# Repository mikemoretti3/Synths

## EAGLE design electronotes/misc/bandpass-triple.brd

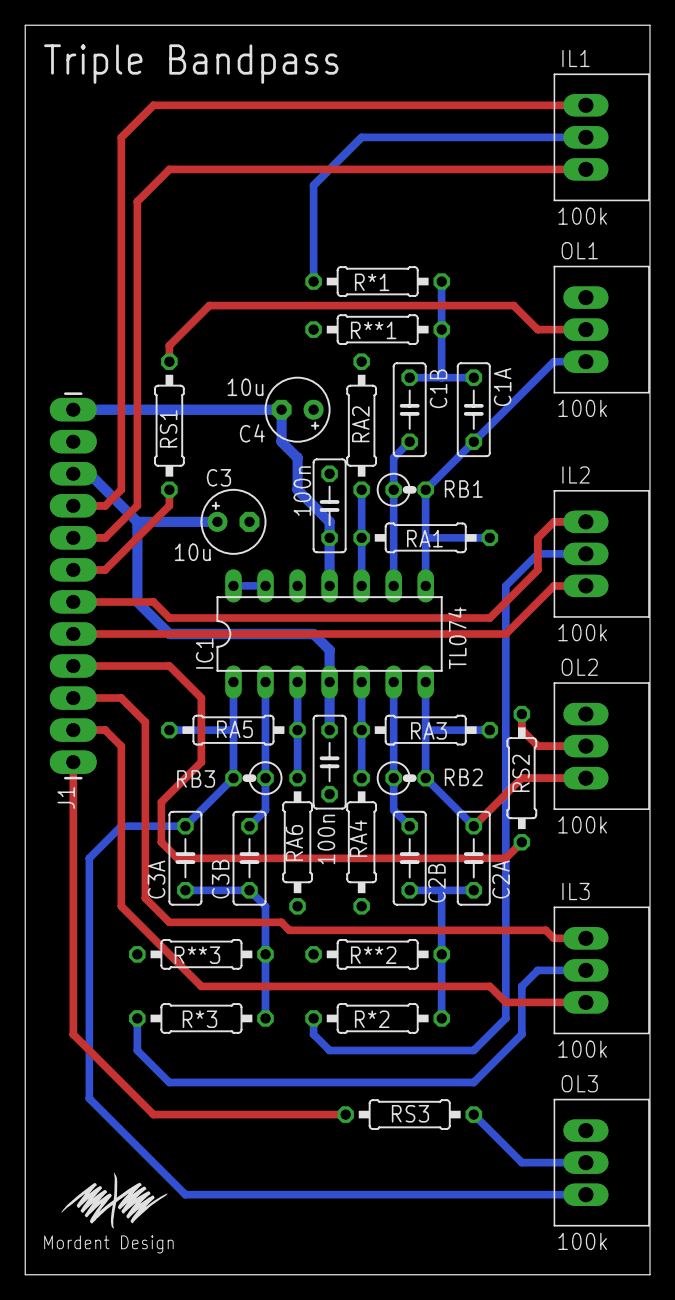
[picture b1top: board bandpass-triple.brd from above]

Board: 2 copper layers, 49.5 x 99.1 mm, 36 parts (0 on the bottom side), 31 nets.

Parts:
C1, C2: 100n; C050-025X075
C1A, C1B, C2A, C2B, C3A, C3B: C050-025X075
C3, C4: 10u; E2,5-5
IC1: TL074; DIL14
IL1, IL2, IL3: 100k; POT-BOURNS-PTD901-2015K
J1: 1X12_LONGPADS
OL1, OL2, OL3: 100k; POT-BOURNS-PTD901-2015K
R*1, R*2, R*3: 0207/10
R**1, R**2, R**3: 0207/10
RA1, RA2, RA3, RA4, RA5, RA6: 0207/10
RB1, RB2, RB3: 0207/2V
RS1, RS2, RS3: 0207/10

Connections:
+12V: C1.1, C3.+, IC1.4, J1.10
-12V: C2.2, C4.-, IC1.11, J1.12
GND: C1.2, C2.1, C3.-, C4.+, IC1.12, J1.11, OL1.3, OL2.3, OL3.3, R**1.1, R**2.1, R**3.1, RA2.1, RA4.1, RA6.1
IN1: IL1.1, J1.8
IN2: IL2.1, J1.5
IN3: IL3.1, J1.2
unnamed: C1B.2, IC1.9, RB1.1
unnamed: C1A.2, IC1.8, OL1.1, RA1.2, RB1.2
unnamed: C1A.1, C1B.1, R*1.2, R**1.2
unnamed: IC1.10, RA1.1, RA2.2
unnamed: C2B.2, IC1.6, RB2.1
unnamed: C2A.2, IC1.7, OL2.1, RA3.2, RB2.2
unnamed: C2A.1, C2B.1, R*2.2, R**2.2
unnamed: IC1.5, RA3.1, RA4.2
unnamed: C3B.2, IC1.2, RB3.1
unnamed: C3A.2, IC1.1, OL3.1, RA5.2, RB3.2
unnamed: C3A.1, C3B.1, R*3.2, R**3.2
unnamed: IC1.3, RA5.1, RA6.2
unnamed: IC1.13, IC1.14
unnamed: IL1.2, R*1.1
unnamed: IL2.2, R*2.1
unnamed: IL3.2, R*3.1
unnamed: OL1.2, RS1.1
unnamed: OL2.2, RS2.1
unnamed: OL3.2, RS3.1
OUT1: J1.7, RS1.2
OUT2: J1.4, RS2.2
OUT3: J1.1, RS3.2
QIN1: IL1.3, J1.9
QIN2: IL2.3, J1.6
QIN3: IL3.3, J1.3

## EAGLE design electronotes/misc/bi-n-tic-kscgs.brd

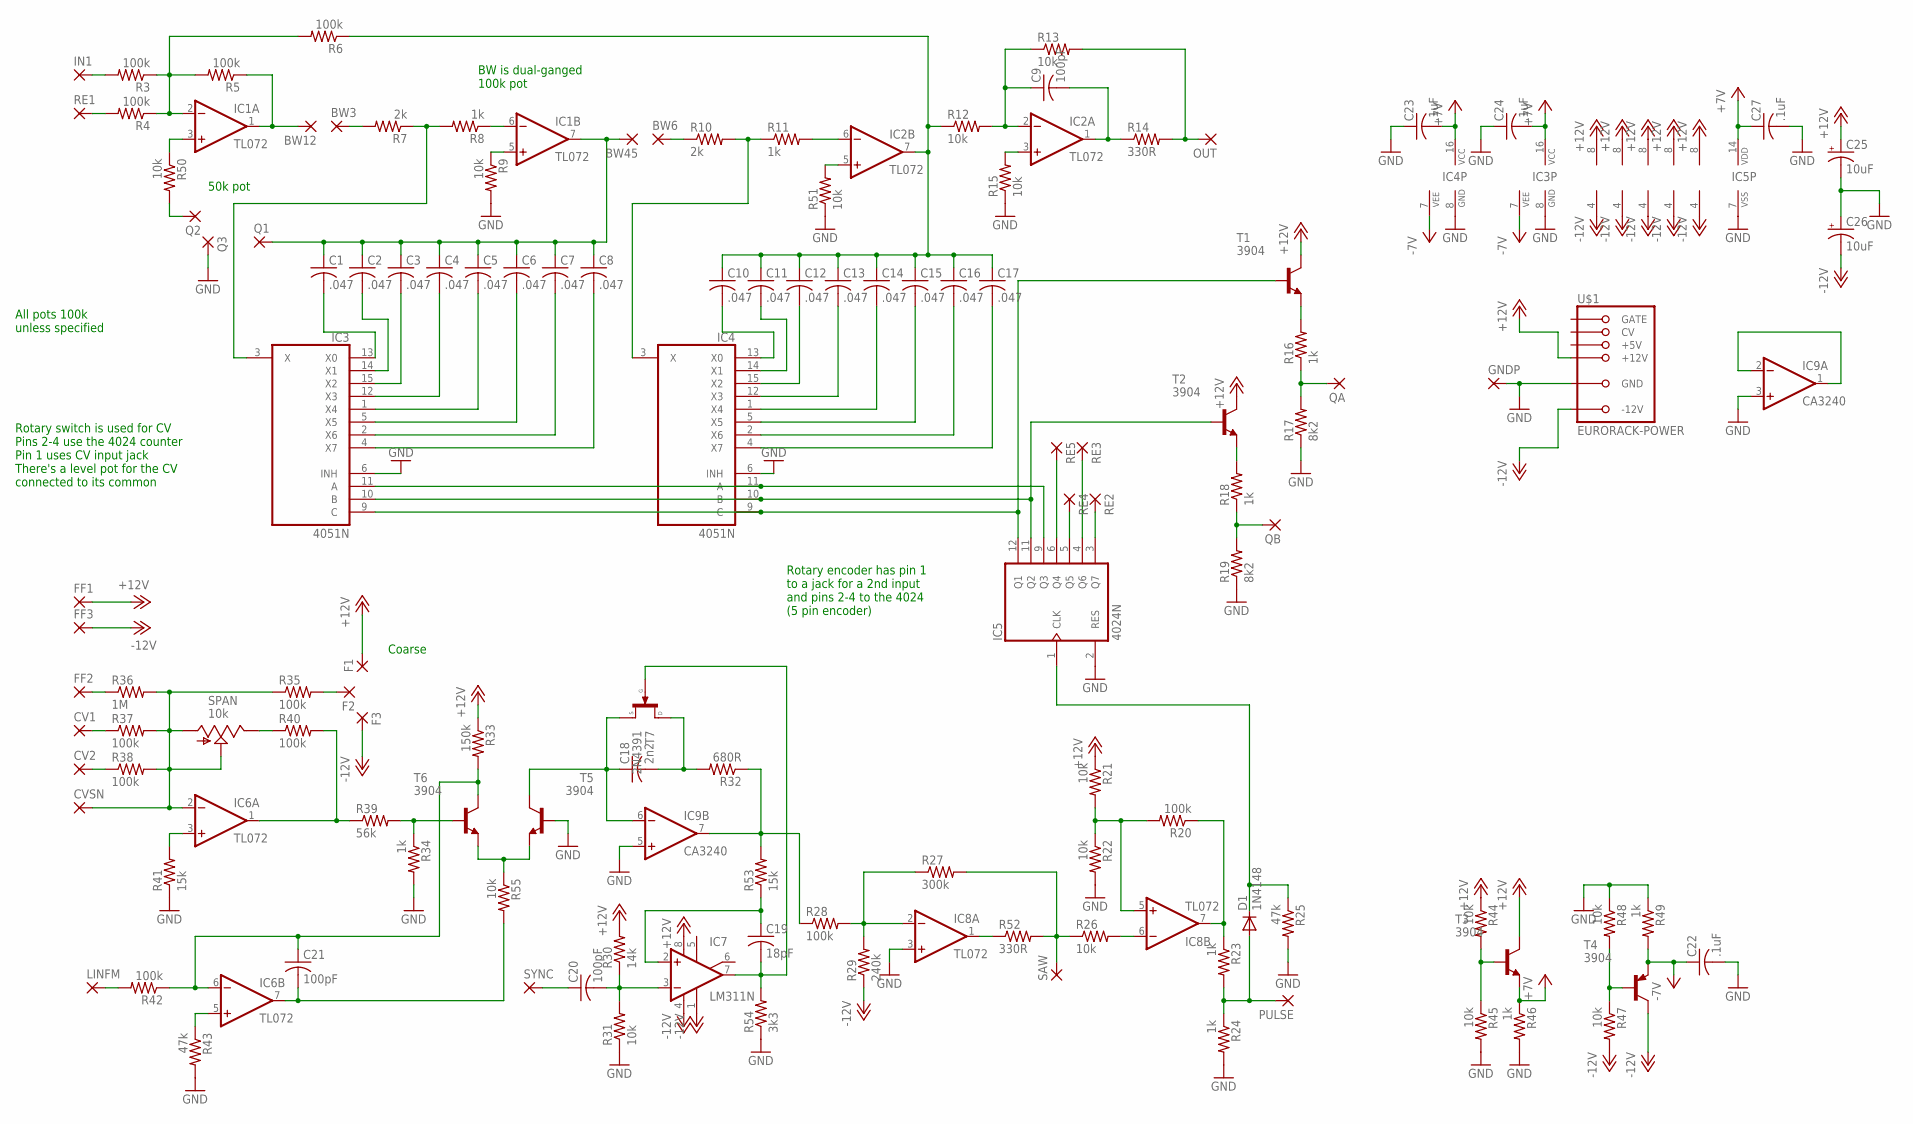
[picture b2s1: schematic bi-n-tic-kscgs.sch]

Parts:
BW3, BW6, BW12, BW45: 2,54/1,0
C1, C2, C3, C4, C5, C6, C7, C8, C10, C11, C12, C13, C14, C15, C16, C17: .047; C050-025X075
C9, C20, C21: 100pF; C050-025X075
C18: 2n2; C050-025X075
C19: 18pF; C050-025X075
C22, C23, C24, C27: .1uF; C050-025X075
C25, C26: 10uF; E2,5-5
CV1, CV2: 2,54/1,0
CVSN: 2,54/1,0
D1: 1N4148; DO35-7
F1, F2, F3: 2,54/1,0
FF1, FF2, FF3: 2,54/1,0
GNDP: 2,54/1,0
IC1, IC2, IC6, IC8: TL072; DIL08
IC3, IC4: 4051N; DIL16
IC5: 4024N; DIL14
IC7: LM311N; DIL08
IC9: CA3240; DIL08
IN1: 2,54/1,0
LINFM: 2,54/1,0
OUT: 2,54/1,0
PULSE: 2,54/1,0
Q1, Q2, Q3: 2,54/1,0
QA: 2,54/1,0
QB: 2,54/1,0
R3, R4, R5, R6, R20, R28, R35, R37, R38, R40, R42: 100k; 0207/10
R7, R10: 2k; 0207/10
R8, R11, R16, R18, R23, R24, R34, R46, R49: 1k; 0207/10
R9, R12, R13, R15, R21, R22, R26, R31, R44, R45, R47, R48, R50, R51, R55: 10k; 0207/10
R14, R52: 330R; 0207/10
R17, R19: 8k2; 0207/10
R25, R43: 47k; 0207/10
R27: 300k; 0207/10
R29: 240k; 0207/10
R30: 14k; 0207/10
R32: 680R; 0207/10
R33: 150k; 0207/10
R36: 1M; 0207/10
R39: 56k; 0207/10
R41, R53: 15k; 0207/10
R54: 3k3; 0207/10
RE1, RE2, RE3, RE4, RE5: 2,54/1,0
SAW: 2,54/1,0
SPAN: 10k; RJ9W
SYNC: 2,54/1,0
T1, T2, T3, T4, T5, T6: 3904; TO92-EBC
T7: 2N4391; TO18E
U$1: EURORACK-POWER; PINSHRD_PTH_2X8

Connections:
+7V: C23.2, C24.2, C27.1, IC3.16 (VCC), IC4.16 (VCC), IC5.14 (VDD), R46.1, T3.E
+12V: C25.+, F1.1, FF1.1, IC1.8 (V+), IC2.8 (V+), IC6.8 (V+), IC7.8 (V+), IC8.8 (V+), IC9.8 (V+), R21.1, R30.2, R33.1, R44.1, T1.C, T2.C, T3.C, U$1.+12V@1 (+12V), U$1.+12V@2 (+12V)
-7V: C22.1, IC3.7 (VEE), IC4.7 (VEE), R49.2, T4.E
-12V: C26.-, F3.1, FF3.1, IC1.4 (V-), IC2.4 (V-), IC6.4 (V-), IC7.1 (GND), IC7.4 (V-), IC8.4 (V-), IC9.4 (V-), R29.1, R47.2, T4.C, U$1.-12V@1 (-12V), U$1.-12V@2 (-12V)
GND: C22.2, C23.1, C24.1, C25.-, C26.+, C27.2, GNDP.1, IC3.6 (INH), IC3.8 (GND), IC4.6 (INH), IC4.8 (GND), IC5.2 (RES), IC5.7 (VSS), IC8.3 (+IN), IC9.3 (+IN), IC9.5 (+IN), Q3.1, R9.2, R15.1, R17.1, R19.1, R22.2, R24.2, R25.2, R31.1, R34.2, R41.1, R43.2, R45.2, R46.2, R48.1, R49.1, R51.1, R54.1, T5.B, U$1.GND@1 (GND), U$1.GND@2 (GND), U$1.GND@3 (GND), U$1.GND@4 (GND), U$1.GND@5 (GND), U$1.GND@6 (GND)
unnamed: IC8.2 (-IN), R27.1, R28.2, R29.2
unnamed: IC1.2 (-IN), R3.1, R4.1, R5.2, R6.2
unnamed: BW12.1, IC1.1 (OUT), R5.1
unnamed: IC1.3 (+IN), R50.1
unnamed: Q2.1, R50.2
unnamed: BW3.1, R7.2
unnamed: IC3.3 (X), R7.1, R8.2
unnamed: IC1.6 (-IN), R8.1
unnamed: C1.2, IC3.13 (X0)
unnamed: C2.2, IC3.14 (X1)
unnamed: C3.2, IC3.15 (X2)
unnamed: C4.2, IC3.12 (X3)
unnamed: C5.2, IC3.1 (X4)
unnamed: C6.2, IC3.5 (X5)
unnamed: C7.2, IC3.2 (X6)
unnamed: C8.2, IC3.4 (X7)
unnamed: BW45.1, C1.1, C2.1, C3.1, C4.1, C5.1, C6.1, C7.1, C8.1, IC1.7 (OUT), Q1.1
unnamed: BW6.1, R10.1
unnamed: IC4.3 (X), R10.2, R11.1
unnamed: IC2.6 (-IN), R11.2
unnamed: C10.1, C11.1, C12.1, C13.1, C14.1, C15.1, C16.1, C17.1, IC2.7 (OUT), R6.1, R12.1
unnamed: C9.1, IC2.2 (-IN), R12.2, R13.1
unnamed: C9.2, IC2.1 (OUT), R14.1
unnamed: OUT.1, R13.2, R14.2
unnamed: IC2.3 (+IN), R15.2
unnamed: IC1.5 (+IN), R9.1
unnamed: C10.2, IC4.13 (X0)
unnamed: C11.2, IC4.14 (X1)
unnamed: C12.2, IC4.15 (X2)
unnamed: C13.2, IC4.12 (X3)
unnamed: C14.2, IC4.1 (X4)
unnamed: C15.2, IC4.5 (X5)
unnamed: C16.2, IC4.2 (X6)
unnamed: C17.2, IC4.4 (X7)
unnamed: IC2.5 (+IN), R51.2
unnamed: R16.2, T1.E
unnamed: FF2.1, R36.1
unnamed: CV1.1, R37.1
unnamed: CV2.1, R38.1
unnamed: LINFM.1, R42.2
unnamed: QA.1, R16.1, R17.2
unnamed: IC3.10 (B), IC4.10 (B), IC5.11 (Q2), T2.B
unnamed: IC3.9 (C), IC4.9 (C), IC5.12 (Q1), T1.B
unnamed: IC3.11 (A), IC4.11 (A), IC5.9 (Q3)
unnamed: R18.2, T2.E
unnamed: QB.1, R18.1, R19.2
unnamed: D1.C, IC5.1 (CLK), R25.1
unnamed: IC9.7 (OUT), R28.1, R32.1, R53.2
unnamed: IC8.5 (+IN), R20.2, R21.2, R22.1
unnamed: IC8.7 (OUT), R20.1, R23.1
unnamed: D1.A, PULSE.1, R23.2, R24.1
unnamed: IC8.6 (-IN), R26.2
unnamed: R26.1, R27.2, R52.2, SAW.1
unnamed: IC8.1 (OUT), R52.1
unnamed: C19.2, IC7.7 (OUT), R54.2, T7.G
unnamed: C18.1, IC9.6 (-IN), T5.C, T7.S
unnamed: C18.2, R32.2, T7.D
unnamed: C19.1, IC7.2 (+IN), R53.1
unnamed: C20.2, IC7.3 (-IN), R30.1, R31.2
unnamed: C20.1, SYNC.1
unnamed: IC9.1 (OUT), IC9.2 (-IN)
unnamed: IC6.5 (+IN), R43.1
unnamed: C21.2, IC6.7 (OUT), R55.2
unnamed: C21.1, IC6.6 (-IN), R33.2, R42.1, T6.C
unnamed: IC6.3 (+IN), R41.2
unnamed: R44.2, R45.1, T3.B
unnamed: CVSN.1, IC6.2 (-IN), R35.1, R36.2, R37.2, R38.2, SPAN.A, SPAN.S
unnamed: R40.1, SPAN.E
unnamed: IC6.1 (OUT), R39.1, R40.2
unnamed: F2.1, R35.2
unnamed: R34.1, R39.2, T6.B
unnamed: IN1.1, R3.2
unnamed: R55.1, T5.E, T6.E
unnamed: R47.1, R48.2, T4.B
unnamed: R4.2, RE1.1
unnamed: IC5.6 (Q4), RE5.1
unnamed: IC5.5 (Q5), RE4.1
unnamed: IC5.3 (Q7), RE2.1
RE3: IC5.4 (Q6), RE3.1

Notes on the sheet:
Rotary encoder has pin 1 to a jack for a 2nd input and pins 2-4 to the 4024 (5 pin encoder)
50k pot
BW is dual-ganged 100k pot
Rotary switch is used for CV Pins 2-4 use the 4024 counter Pin 1 uses CV input jack There's a level pot for the CV connected to its common
Coarse
All pots 100k unless specified

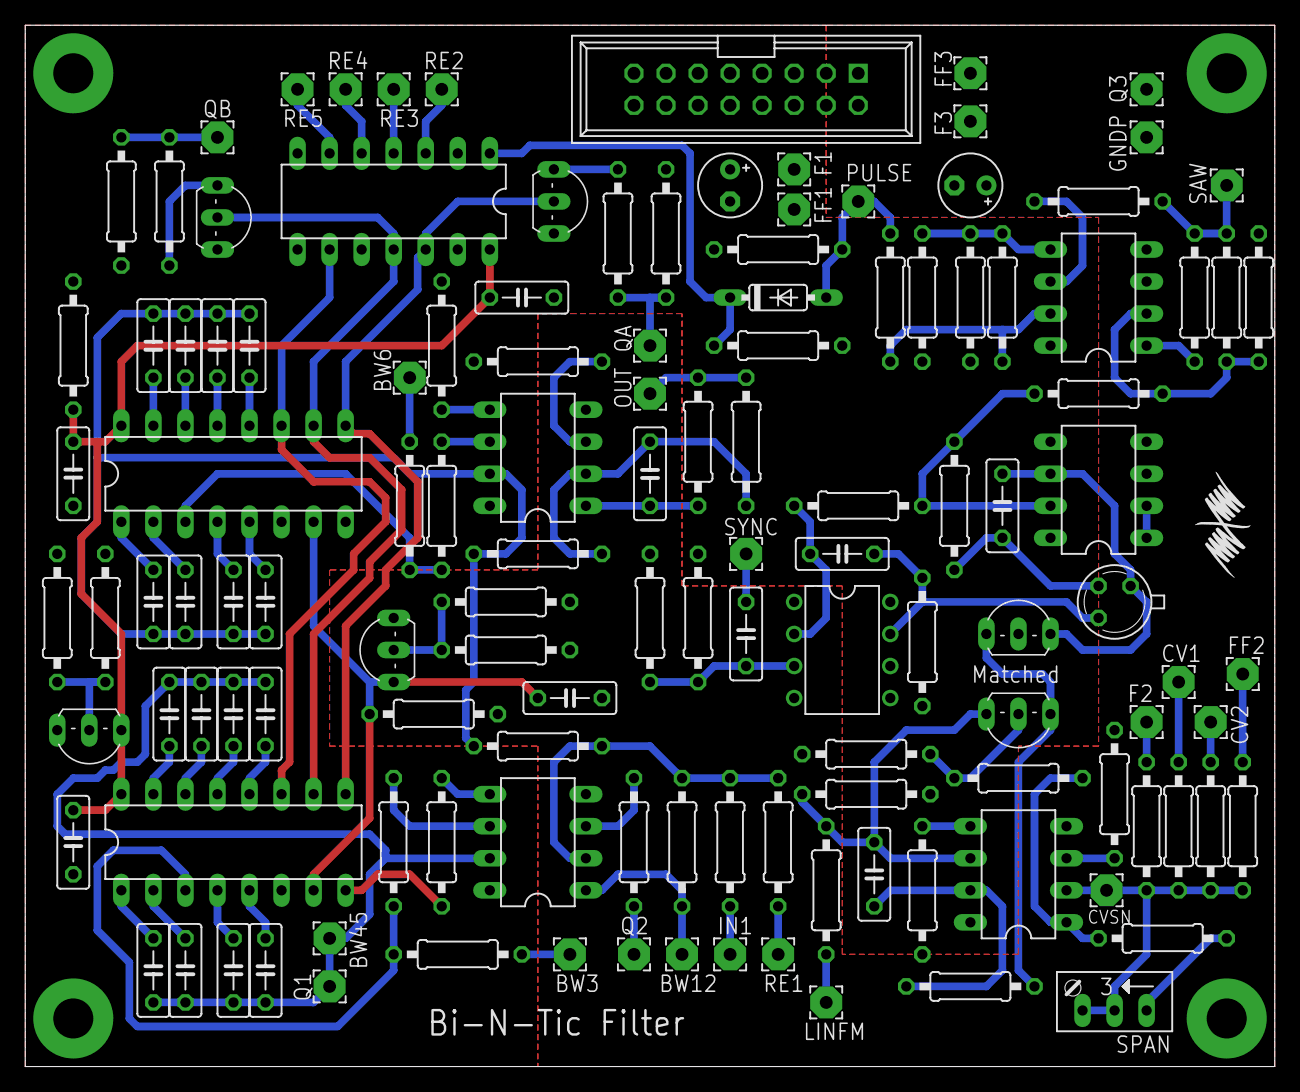
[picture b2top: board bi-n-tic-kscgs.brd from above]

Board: 2 copper layers, 99.1 x 82.5 mm, 129 parts (0 on the bottom side), 84 nets.

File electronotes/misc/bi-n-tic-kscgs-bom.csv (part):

"Part";"Value";"Device";"Package";"Description";"";
"BW3";"";"2,54/1,0";"2,54/1,0";"THROUGH-HOLE PAD";"";
"BW6";"";"2,54/1,0";"2,54/1,0";"THROUGH-HOLE PAD";"";
"BW12";"";"2,54/1,0";"2,54/1,0";"THROUGH-HOLE PAD";"";
"BW45";"";"2,54/1,0";"2,54/1,0";"THROUGH-HOLE PAD";"";
"C1";".047";"C-US050-025X075";"C050-025X075";"CAPACITOR, American symbol";"";
"C2";".047";"C-US050-025X075";"C050-025X075";"CAPACITOR, American symbol";"";
"C3";".047";"C-US050-025X075";"C050-025X075";"CAPACITOR, American symbol";"";
"C4";".047";"C-US050-025X075";"C050-025X075";"CAPACITOR, American symbol";"";
"C5";".047";"C-US050-025X075";"C050-025X075";"CAPACITOR, American symbol";"";
"C6";".047";"C-US050-025X075";"C050-025X075";"CAPACITOR, American symbol";"";
"C7";".047";"C-US050-025X075";"C050-025X075";"CAPACITOR, American symbol";"";
"C8";".047";"C-US050-025X075";"C050-025X075";"CAPACITOR, American symbol";"";
"C9";"100pF";"C-US050-025X075";"C050-025X075";"CAPACITOR, American symbol";"";
"C10";".047";"C-US050-025X075";"C050-025X075";"CAPACITOR, American symbol";"";
"C11";".047";"C-US050-025X075";"C050-025X075";"CAPACITOR, American symbol";"";
"C12";".047";"C-US050-025X075";"C050-025X075";"CAPACITOR, American symbol";"";
"C13";".047";"C-US050-025X075";"C050-025X075";"CAPACITOR, American symbol";"";
"C14";".047";"C-US050-025X075";"C050-025X075";"CAPACITOR, American symbol";"";
"C15";".047";"C-US050-025X075";"C050-025X075";"CAPACITOR, American symbol";"";
"C16";".047";"C-US050-025X075";"C050-025X075";"CAPACITOR, American symbol";"";
"C17";".047";"C-US050-025X075";"C050-025X075";"CAPACITOR, American symbol";"";
"C18";"2n2";"C-US050-025X075";"C050-025X075";"CAPACITOR, American symbol";"";
"C19";"18pF";"C-US050-025X075";"C050-025X075";"CAPACITOR, American symbol";"";
"C20";"100pF";"C-US050-025X075";"C050-025X075";"CAPACITOR, American symbol";"";
"C21";"100pF";"C-US050-025X075";"C050-025X075";"CAPACITOR, American symbol";"";
"C22";".1uF";"C-US050-025X075";"C050-025X075";"CAPACITOR, American symbol";"";
"C23";".1uF";"C-US050-025X075";"C050-025X075";"CAPACITOR, American symbol";"";
"C24";".1uF";"C-US050-025X075";"C050-025X075";"CAPACITOR, American symbol";"";
"C25";"10uF";"CPOL-USE2.5-5";"E2,5-5";"POLARIZED CAPACITOR, American symbol";"";
"C26";"10uF";"CPOL-USE2.5-5";"E2,5-5";"POLARIZED CAPACITOR, American symbol";"";
"C27";".1uF";"C-US050-025X075";"C050-025X075";"CAPACITOR, American symbol";"";
"CV1";"";"2,54/1,0";"2,54/1,0";"THROUGH-HOLE PAD";"";
"CV2";"";"2,54/1,0";"2,54/1,0";"THROUGH-HOLE PAD";"";
"CVSN";"";"2,54/1,0";"2,54/1,0";"THROUGH-HOLE PAD";"";
"D1";"1N4148";"1N4148DO35-7";"DO35-7";"DIODE";"";
"F1";"";"2,54/1,0";"2,54/1,0";"THROUGH-HOLE PAD";"";
"F2";"";"2,54/1,0";"2,54/1,0";"THROUGH-HOLE PAD";"";
"F3";"";"2,54/1,0";"2,54/1,0";"THROUGH-HOLE PAD";"";
"FF1";"";"2,54/1,0";"2,54/1,0";"THROUGH-HOLE PAD";"";
"FF2";"";"2,54/1,0";"2,54/1,0";"THROUGH-HOLE PAD";"";
"FF3";"";"2,54/1,0";"2,54/1,0";"THROUGH-HOLE PAD";"";
"GNDP";"";"2,54/1,0";"2,54/1,0";"THROUGH-HOLE PAD";"";
"IC1";"TL072";"TL072-TOPP";"DIL08";"OP AMP";"";
"IC2";"TL072";"TL072-TOPP";"DIL08";"OP AMP";"";
"IC3";"4051N";"4051N";"DIL16";"8-channel ANALOG MULTIPLEXER";"";
"IC4";"4051N";"4051N";"DIL16";"8-channel ANALOG MULTIPLEXER";"";
"IC5";"4024N";"4024N";"DIL14";"7-stage binary/ripple COUNTER";"";
"IC6";"TL072";"TL072-TOPP";"DIL08";"OP AMP";"";
"IC7";"LM311N";"LM311N";"DIL08";"COMPARATOR";"";
"IC8";"TL072";"TL072-TOPP";"DIL08";"OP AMP";"";
"IC9";"CA3240";"TL072-TOPP";"DIL08";"OP AMP";"";
"IN1";"";"2,54/1,0";"2,54/1,0";"THROUGH-HOLE PAD";"";
"LINFM";"";"2,54/1,0";"2,54/1,0";"THROUGH-HOLE PAD";"";
"OUT";"";"2,54/1,0";"2,54/1,0";"THROUGH-HOLE PAD";"";
"PULSE";"";"2,54/1,0";"2,54/1,0";"THROUGH-HOLE PAD";"";
"Q1";"";"2,54/1,0";"2,54/1,0";"THROUGH-HOLE PAD";"";
"Q2";"";"2,54/1,0";"2,54/1,0";"THROUGH-HOLE PAD";"";
"Q3";"";"2,54/1,0";"2,54/1,0";"THROUGH-HOLE PAD";"";
"QA";"";"2,54/1,0";"2,54/1,0";"THROUGH-HOLE PAD";"";
"QB";"";"2,54/1,0";"2,54/1,0";"THROUGH-HOLE PAD";"";
"R3";"100k";"R-US_0207/10";"0207/10";"RESISTOR, American symbol";"";
"R4";"100k";"R-US_0207/10";"0207/10";"RESISTOR, American symbol";"";
"R5";"100k";"R-US_0207/10";"0207/10";"RESISTOR, American symbol";"";
"R6";"100k";"R-US_0207/10";"0207/10";"RESISTOR, American symbol";"";
"R7";"2k";"R-US_0207/10";"0207/10";"RESISTOR, American symbol";"";
"R8";"1k";"R-US_0207/10";"0207/10";"RESISTOR, American symbol";"";
"R9";"10k";"R-US_0207/10";"0207/10";"RESISTOR, American symbol";"";
"R10";"2k";"R-US_0207/10";"0207/10";"RESISTOR, American symbol";"";
"R11";"1k";"R-US_0207/10";"0207/10";"RESISTOR, American symbol";"";
"R12";"10k";"R-US_0207/10";"0207/10";"RESISTOR, American symbol";"";
"R13";"10k";"R-US_0207/10";"0207/10";"RESISTOR, American symbol";"";
"R14";"330R";"R-US_0207/10";"0207/10";"RESISTOR, American symbol";"";
"R15";"10k";"R-US_0207/10";"0207/10";"RESISTOR, American symbol";"";
"R16";"1k";"R-US_0207/10";"0207/10";"RESISTOR, American symbol";"";
"R17";"8k2";"R-US_0207/10";"0207/10";"RESISTOR, American symbol";"";
"R18";"1k";"R-US_0207/10";"0207/10";"RESISTOR, American symbol";"";
"R19";"8k2";"R-US_0207/10";"0207/10";"RESISTOR, American symbol";"";
"R20";"100k";"R-US_0207/10";"0207/10";"RESISTOR, American symbol";"";
"R21";"10k";"R-US_0207/10";"0207/10";"RESISTOR, American symbol";"";
"R22";"10k";"R-US_0207/10";"0207/10";"RESISTOR, American symbol";"";
"R23";"1k";"R-US_0207/10";"0207/10";"RESISTOR, American symbol";"";
"R24";"1k";"R-US_0207/10";"0207/10";"RESISTOR, American symbol";"";
"R25";"47k";"R-US_0207/10";"0207/10";"RESISTOR, American symbol";"";
"R26";"10k";"R-US_0207/10";"0207/10";"RESISTOR, American symbol";"";
"R27";"300k";"R-US_0207/10";"0207/10";"RESISTOR, American symbol";"";
"R28";"100k";"R-US_0207/10";"0207/10";"RESISTOR, American symbol";"";
"R29";"240k";"R-US_0207/10";"0207/10";"RESISTOR, American symbol";"";
"R30";"14k";"R-US_0207/10";"0207/10";"RESISTOR, American symbol";"";
"R31";"10k";"R-US_0207/10";"0207/10";"RESISTOR, American symbol";"";
"R32";"680R";"R-US_0207/10";"0207/10";"RESISTOR, American symbol";"";
"R33";"150k";"R-US_0207/10";"0207/10";"RESISTOR, American symbol";"";
"R34";"1k";"R-US_0207/10";"0207/10";"RESISTOR, American symbol";"";
"R35";"100k";"R-US_0207/10";"0207/10";"RESISTOR, American symbol";"";
"R36";"1M";"R-US_0207/10";"0207/10";"RESISTOR, American symbol";"";
"R37";"100k";"R-US_0207/10";"0207/10";"RESISTOR, American symbol";"";
"R38";"100k";"R-US_0207/10";"0207/10";"RESISTOR, American symbol";"";
"R39";"56k";"R-US_0207/10";"0207/10";"RESISTOR, American symbol";"";
"R40";"100k";"R-US_0207/10";"0207/10";"RESISTOR, American symbol";"";
"R41";"15k";"R-US_0207/10";"0207/10";"RESISTOR, American symbol";"";
"R42";"100k";"R-US_0207/10";"0207/10";"RESISTOR, American symbol";"";
"R43";"47k";"R-US_0207/10";"0207/10";"RESISTOR, American symbol";"";
"R44";"10k";"R-US_0207/10";"0207/10";"RESISTOR, American symbol";"";
"R45";"10k";"R-US_0207/10";"0207/10";"RESISTOR, American symbol";"";
"R46";"1k";"R-US_0207/10";"0207/10";"RESISTOR, American symbol";"";
"R47";"10k";"R-US_0207/10";"0207/10";"RESISTOR, American symbol";"";
"R48";"10k";"R-US_0207/10";"0207/10";"RESISTOR, American symbol";"";
"R49";"1k";"R-US_0207/10";"0207/10";"RESISTOR, American symbol";"";
"R50";"10k";"R-US_0207/10";"0207/10";"RESISTOR, American symbol";"";
"R51";"10k";"R-US_0207/10";"0207/10";"RESISTOR, American symbol";"";
"R52";"330R";"R-US_0207/10";"0207/10";"RESISTOR, American symbol";"";
"R53";"15k";"R-US_0207/10";"0207/10";"RESISTOR, American symbol";"";
"R54";"3k3";"R-US_0207/10";"0207/10";"RESISTOR, American symbol";"";
"R55";"10k";"R-US_0207/10";"0207/10";"RESISTOR, American symbol";"";
"RE1";"";"2,54/1,0";"2,54/1,0";"THROUGH-HOLE PAD";"";
"RE2";"";"2,54/1,0";"2,54/1,0";"THROUGH-HOLE PAD";"";
"RE3";"";"2,54/1,0";"2,54/1,0";"THROUGH-HOLE PAD";"";
"RE4";"";"2,54/1,0";"2,54/1,0";"THROUGH-HOLE PAD";"";
"RE5";"";"2,54/1,0";"2,54/1,0";"THROUGH-HOLE PAD";"";
"SAW";"";"2,54/1,0";"2,54/1,0";"THROUGH-HOLE PAD";"";
"SPAN";"10k";"TRIM_US-RJ9W";"RJ9W";"POTENTIOMETER";"";
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
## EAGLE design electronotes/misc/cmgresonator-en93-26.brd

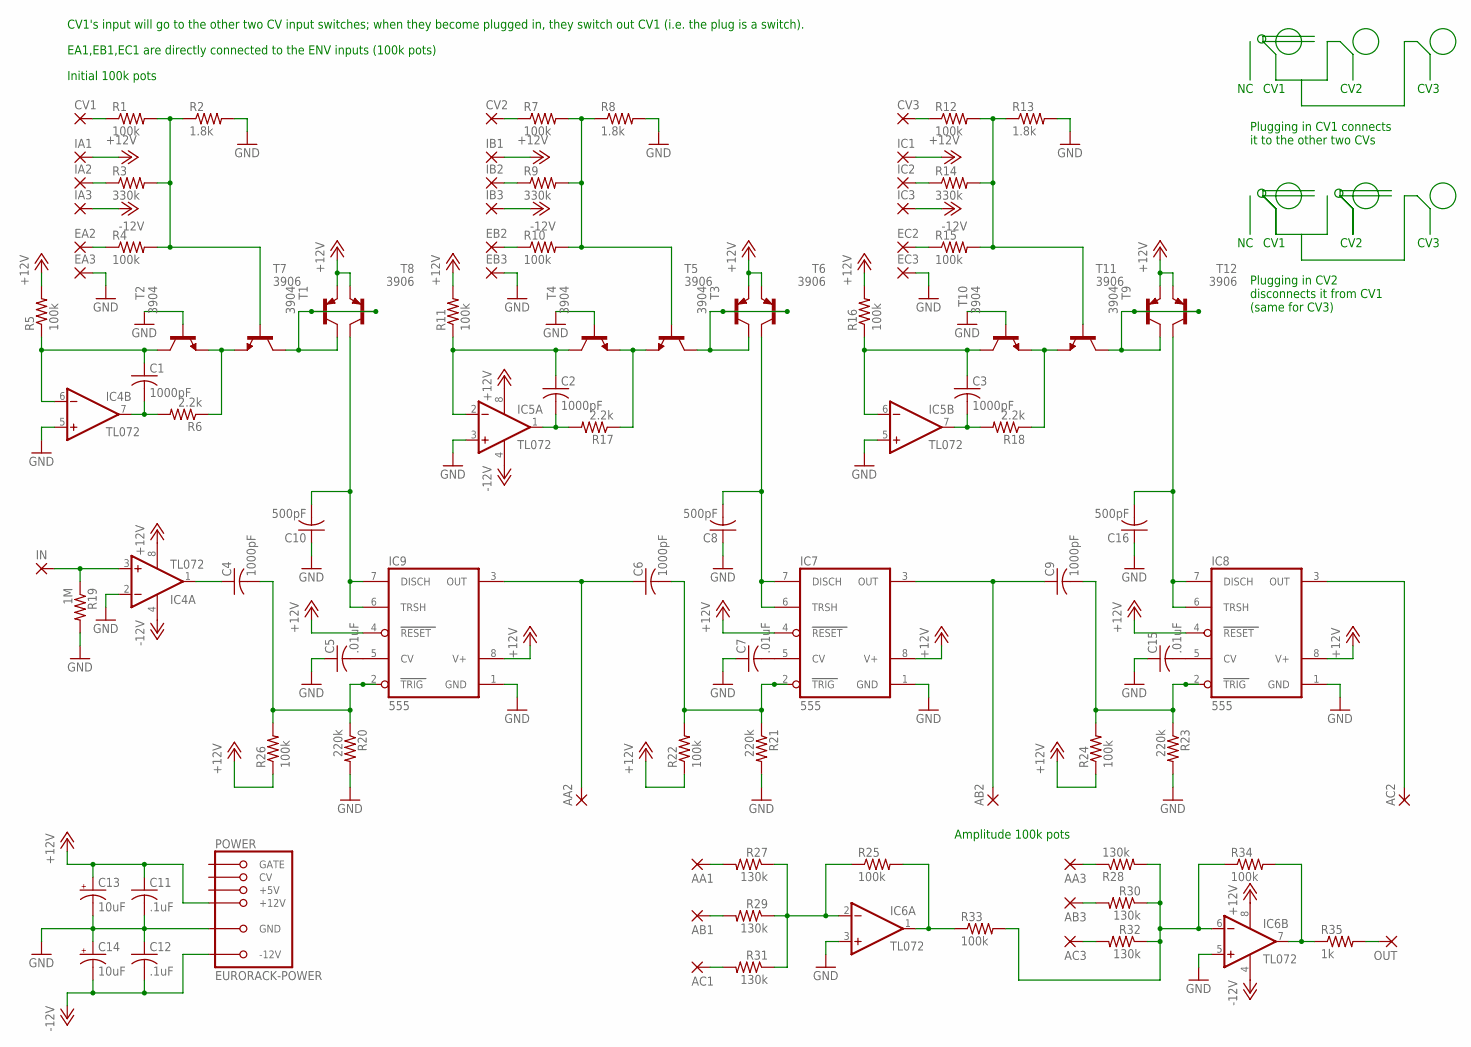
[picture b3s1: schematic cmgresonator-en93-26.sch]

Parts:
AA1, AA2, AA3: 2,54/1,0
AB1, AB2, AB3: 2,54/1,0
AC1, AC2, AC3: 2,54/1,0
C1, C2, C3, C4, C6, C9: 1000pF; C050-025X075
C5, C7, C15: .01uF; C050-025X075
C8, C10, C16: 500pF; C050-025X075
C11, C12: .1uF; C050-025X075
C13, C14: 10uF; E2,5-5
CV1, CV2, CV3: 2,54/1,0
EA2, EA3: 2,54/1,0
EB2, EB3: 2,54/1,0
EC2, EC3: 2,54/1,0
IA1, IA2, IA3: 2,54/1,0
IB1, IB2, IB3: 2,54/1,0
IC1, IC2, IC3: 2,54/1,0
IC4, IC5, IC6: TL072; DIL08
IC7, IC8, IC9: 555; DIL08
IN: 2,54/1,0
OUT: 2,54/1,0
POWER: EURORACK-POWER; PINSHRD_PTH_2X8
R1, R4, R5, R7, R10, R11, R12, R15, R16, R22, R24, R25, R26, R33, R34: 100k; 0207/10
R2, R8, R13: 1.8k; 0207/10
R3, R9, R14: 330k; 0207/10
R6, R17, R18: 2.2k; 0207/10
R19: 1M; 0207/10
R20, R21, R23: 220k; 0207/10
R27, R28, R29, R30, R31, R32: 130k; 0207/10
R35: 1k; 0207/10
T1, T2, T3, T4, T9, T10: 3904; TO92-EBC
T5, T6, T7, T8, T11, T12: 3906; TO92-EBC

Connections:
+12V: C11.1, C13.+, IA1.1, IB1.1, IC1.1, IC4.8 (V+), IC5.8 (V+), IC6.8 (V+), IC7.4 (RESET), IC7.8 (V+), IC8.4 (RESET), IC8.8 (V+), IC9.4 (RESET), IC9.8 (V+), POWER.+12V@1 (+12V), POWER.+12V@2 (+12V), R5.2, R11.2, R16.2, R22.1, R24.1, R26.1, T5.E, T6.E, T7.E, T8.E, T11.E, T12.E
-12V: C12.2, C14.-, IA3.1, IB3.1, IC3.1, IC4.4 (V-), IC5.4 (V-), IC6.4 (V-), POWER.-12V@1 (-12V), POWER.-12V@2 (-12V)
GND: C5.1, C7.1, C8.1, C10.1, C11.2, C12.1, C13.-, C14.+, C15.1, C16.1, EA3.1, EB3.1, EC3.1, IC4.2 (-IN), IC4.5 (+IN), IC5.3 (+IN), IC5.5 (+IN), IC6.3 (+IN), IC6.5 (+IN), IC7.1 (GND), IC8.1 (GND), IC9.1 (GND), POWER.GND@1 (GND), POWER.GND@2 (GND), POWER.GND@3 (GND), POWER.GND@4 (GND), POWER.GND@5 (GND), POWER.GND@6 (GND), R2.2, R8.2, R13.2, R19.2, R20.2, R21.2, R23.2, T2.B, T4.B, T10.B
unnamed: R6.1, T1.E, T2.E
unnamed: R17.1, T3.E, T4.E
unnamed: C1.1, IC4.6 (-IN), R5.1, T2.C
unnamed: T1.C, T7.B, T7.C, T8.B
unnamed: CV1.1, R1.1
unnamed: R1.2, R2.1, R3.2, R4.2, T1.B
unnamed: IA2.1, R3.1
unnamed: EA2.1, R4.1
unnamed: C2.1, IC5.2 (-IN), R11.1, T4.C
unnamed: T3.C, T5.B, T5.C, T6.B
unnamed: CV2.1, R7.1
unnamed: R7.2, R8.1, R9.2, R10.2, T3.B
unnamed: IB2.1, R9.1
unnamed: EB2.1, R10.1
unnamed: R18.1, T9.E, T10.E
unnamed: C3.1, IC5.6 (-IN), R16.1, T10.C
unnamed: T9.C, T11.B, T11.C, T12.B
unnamed: CV3.1, R12.1
unnamed: R12.2, R13.1, R14.2, R15.2, T9.B
unnamed: IC2.1, R14.1
unnamed: EC2.1, R15.1
unnamed: C10.2, IC9.6 (TRSH), IC9.7 (DISCH), T8.C
unnamed: C5.2, IC9.5 (CV)
unnamed: C8.2, IC7.6 (TRSH), IC7.7 (DISCH), T6.C
unnamed: C4.2, IC9.2 (TRIG), R20.1, R26.2
unnamed: C7.2, IC7.5 (CV)
unnamed: C6.2, IC7.2 (TRIG), R21.1, R22.2
unnamed: C16.2, IC8.6 (TRSH), IC8.7 (DISCH), T12.C
unnamed: C15.2, IC8.5 (CV)
unnamed: C9.2, IC8.2 (TRIG), R23.1, R24.2
unnamed: AA2.1, C6.1, IC9.3 (OUT)
unnamed: AB2.1, C9.1, IC7.3 (OUT)
unnamed: C4.1, IC4.1 (OUT)
unnamed: IC4.3 (+IN), IN.1, R19.1
unnamed: AA1.1, R27.2
unnamed: AA3.1, R28.1
unnamed: AC2.1, IC8.3 (OUT)
unnamed: AB1.1, R29.2
unnamed: AC1.1, R31.2
unnamed: AB3.1, R30.2
unnamed: AC3.1, R32.2
unnamed: IC6.6 (-IN), R28.2, R30.1, R32.1, R33.2, R34.1
unnamed: IC6.7 (OUT), R34.2, R35.1
unnamed: OUT.1, R35.2
unnamed: IC6.1 (OUT), R25.2, R33.1
unnamed: C2.2, IC5.1 (OUT), R17.2
unnamed: IC6.2 (-IN), R25.1, R27.1, R29.1, R31.1
unnamed: C1.2, IC4.7 (OUT), R6.2
unnamed: C3.2, IC5.7 (OUT), R18.2

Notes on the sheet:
CV1's input will go to the other two CV input switches; when they become plugged in, they switch out CV1 (i.e. the plug is a switch).
EA1,EB1,EC1 are directly connected to the ENV inputs (100k pots)
Amplitude 100k pots
Initial 100k pots
CV1
CV2
CV3
Plugging in CV1 connects it to the other two CVs
Plugging in CV2 disconnects it from CV1 (same for CV3)

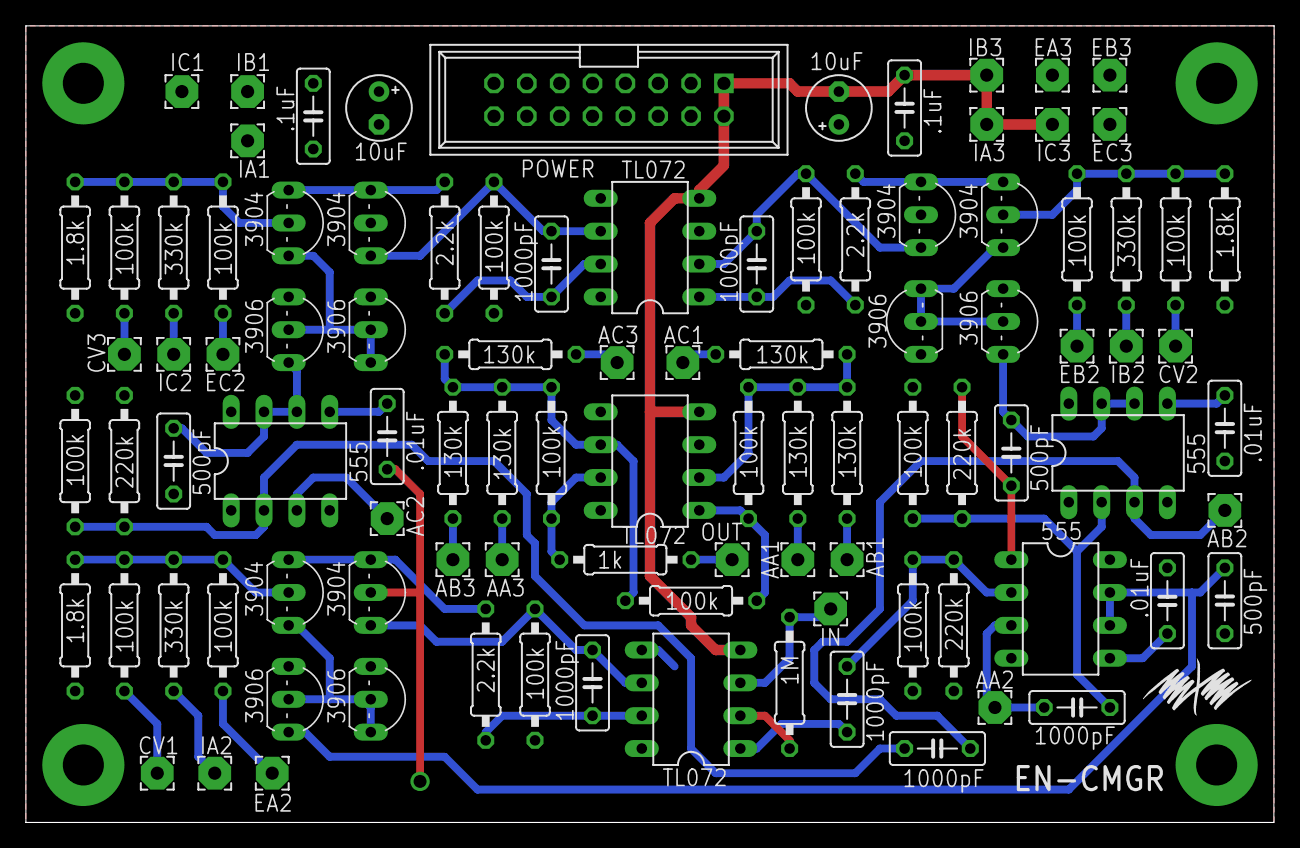
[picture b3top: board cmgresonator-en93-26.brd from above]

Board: 2 copper layers, 96.5 x 61.6 mm, 99 parts (0 on the bottom side), 52 nets.

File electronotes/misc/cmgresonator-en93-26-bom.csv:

"Part";"Value";"Device";"Package";"Description";"MF";"MPN";"OC_FARNELL";"OC_NEWARK";
"AA1";"";"2,54/1,0";"2,54/1,0";"THROUGH-HOLE PAD";"";"";"";"";
"AA2";"";"2,54/1,0";"2,54/1,0";"THROUGH-HOLE PAD";"";"";"";"";
"AA3";"";"2,54/1,0";"2,54/1,0";"THROUGH-HOLE PAD";"";"";"";"";
"AB1";"";"2,54/1,0";"2,54/1,0";"THROUGH-HOLE PAD";"";"";"";"";
"AB2";"";"2,54/1,0";"2,54/1,0";"THROUGH-HOLE PAD";"";"";"";"";
"AB3";"";"2,54/1,0";"2,54/1,0";"THROUGH-HOLE PAD";"";"";"";"";
"AC1";"";"2,54/1,0";"2,54/1,0";"THROUGH-HOLE PAD";"";"";"";"";
"AC2";"";"2,54/1,0";"2,54/1,0";"THROUGH-HOLE PAD";"";"";"";"";
"AC3";"";"2,54/1,0";"2,54/1,0";"THROUGH-HOLE PAD";"";"";"";"";
"C1";"1000pF";"C-US050-025X075";"C050-025X075";"CAPACITOR, American symbol";"";"";"";"";
"C2";"1000pF";"C-US050-025X075";"C050-025X075";"CAPACITOR, American symbol";"";"";"";"";
"C3";"1000pF";"C-US050-025X075";"C050-025X075";"CAPACITOR, American symbol";"";"";"";"";
"C4";"1000pF";"C-US050-025X075";"C050-025X075";"CAPACITOR, American symbol";"";"";"";"";
"C5";".01uF";"C-US050-025X075";"C050-025X075";"CAPACITOR, American symbol";"";"";"";"";
"C6";"1000pF";"C-US050-025X075";"C050-025X075";"CAPACITOR, American symbol";"";"";"";"";
"C7";".01uF";"C-US050-025X075";"C050-025X075";"CAPACITOR, American symbol";"";"";"";"";
"C8";"500pF";"C-US050-025X075";"C050-025X075";"CAPACITOR, American symbol";"";"";"";"";
"C9";"1000pF";"C-US050-025X075";"C050-025X075";"CAPACITOR, American symbol";"";"";"";"";
"C10";"500pF";"C-US050-025X075";"C050-025X075";"CAPACITOR, American symbol";"";"";"";"";
"C11";".1uF";"C-US050-025X075";"C050-025X075";"CAPACITOR, American symbol";"";"";"";"";
"C12";".1uF";"C-US050-025X075";"C050-025X075";"CAPACITOR, American symbol";"";"";"";"";
"C13";"10uF";"CPOL-USE2.5-5";"E2,5-5";"POLARIZED CAPACITOR, American symbol";"";"";"";"";
"C14";"10uF";"CPOL-USE2.5-5";"E2,5-5";"POLARIZED CAPACITOR, American symbol";"";"";"";"";
"C15";".01uF";"C-US050-025X075";"C050-025X075";"CAPACITOR, American symbol";"";"";"";"";
"C16";"500pF";"C-US050-025X075";"C050-025X075";"CAPACITOR, American symbol";"";"";"";"";
"CV1";"";"2,54/1,0";"2,54/1,0";"THROUGH-HOLE PAD";"";"";"";"";
"CV2";"";"2,54/1,0";"2,54/1,0";"THROUGH-HOLE PAD";"";"";"";"";
"CV3";"";"2,54/1,0";"2,54/1,0";"THROUGH-HOLE PAD";"";"";"";"";
"EA2";"";"2,54/1,0";"2,54/1,0";"THROUGH-HOLE PAD";"";"";"";"";
"EA3";"";"2,54/1,0";"2,54/1,0";"THROUGH-HOLE PAD";"";"";"";"";
"EB2";"";"2,54/1,0";"2,54/1,0";"THROUGH-HOLE PAD";"";"";"";"";
"EB3";"";"2,54/1,0";"2,54/1,0";"THROUGH-HOLE PAD";"";"";"";"";
"EC2";"";"2,54/1,0";"2,54/1,0";"THROUGH-HOLE PAD";"";"";"";"";
"EC3";"";"2,54/1,0";"2,54/1,0";"THROUGH-HOLE PAD";"";"";"";"";
"IA1";"";"2,54/1,0";"2,54/1,0";"THROUGH-HOLE PAD";"";"";"";"";
"IA2";"";"2,54/1,0";"2,54/1,0";"THROUGH-HOLE PAD";"";"";"";"";
"IA3";"";"2,54/1,0";"2,54/1,0";"THROUGH-HOLE PAD";"";"";"";"";
"IB1";"";"2,54/1,0";"2,54/1,0";"THROUGH-HOLE PAD";"";"";"";"";
"IB2";"";"2,54/1,0";"2,54/1,0";"THROUGH-HOLE PAD";"";"";"";"";
"IB3";"";"2,54/1,0";"2,54/1,0";"THROUGH-HOLE PAD";"";"";"";"";
"IC1";"";"2,54/1,0";"2,54/1,0";"THROUGH-HOLE PAD";"";"";"";"";
"IC2";"";"2,54/1,0";"2,54/1,0";"THROUGH-HOLE PAD";"";"";"";"";
"IC3";"";"2,54/1,0";"2,54/1,0";"THROUGH-HOLE PAD";"";"";"";"";
"IC4";"TL072";"TL072-TOPP";"DIL08";"OP AMP";"";"";"";"";
"IC5";"TL072";"TL072-TOPP";"DIL08";"OP AMP";"";"";"";"";
"IC6";"TL072";"TL072-TOPP";"DIL08";"OP AMP";"";"";"";"";
"IC7";"555";"ICM7555";"DIL08";"TIMER";"MAXIM";"ICM7555IPA+";"9663762";"68K4387";
"IC8";"555";"ICM7555";"DIL08";"TIMER";"MAXIM";"ICM7555IPA+";"9663762";"68K4387";
"IC9";"555";"ICM7555";"DIL08";"TIMER";"MAXIM";"ICM7555IPA+";"9663762";"68K4387";
"IN";"";"2,54/1,0";"2,54/1,0";"THROUGH-HOLE PAD";"";"";"";"";
"OUT";"";"2,54/1,0";"2,54/1,0";"THROUGH-HOLE PAD";"";"";"";"";
"POWER";"EURORACK-POWER";"EURORACK-POWER";"PINSHRD_PTH_2X8";"";"";"";"";"";
"R1";"100k";"R-US_0207/10";"0207/10";"RESISTOR, American symbol";"";"";"";"";
"R2";"1.8k";"R-US_0207/10";"0207/10";"RESISTOR, American symbol";"";"";"";"";
"R3";"330k";"R-US_0207/10";"0207/10";"RESISTOR, American symbol";"";"";"";"";
"R4";"100k";"R-US_0207/10";"0207/10";"RESISTOR, American symbol";"";"";"";"";
"R5";"100k";"R-US_0207/10";"0207/10";"RESISTOR, American symbol";"";"";"";"";
"R6";"2.2k";"R-US_0207/10";"0207/10";"RESISTOR, American symbol";"";"";"";"";
"R7";"100k";"R-US_0207/10";"0207/10";"RESISTOR, American symbol";"";"";"";"";
"R8";"1.8k";"R-US_0207/10";"0207/10";"RESISTOR, American symbol";"";"";"";"";
"R9";"330k";"R-US_0207/10";"0207/10";"RESISTOR, American symbol";"";"";"";"";
"R10";"100k";"R-US_0207/10";"0207/10";"RESISTOR, American symbol";"";"";"";"";
"R11";"100k";"R-US_0207/10";"0207/10";"RESISTOR, American symbol";"";"";"";"";
"R12";"100k";"R-US_0207/10";"0207/10";"RESISTOR, American symbol";"";"";"";"";
"R13";"1.8k";"R-US_0207/10";"0207/10";"RESISTOR, American symbol";"";"";"";"";
"R14";"330k";"R-US_0207/10";"0207/10";"RESISTOR, American symbol";"";"";"";"";
"R15";"100k";"R-US_0207/10";"0207/10";"RESISTOR, American symbol";"";"";"";"";
"R16";"100k";"R-US_0207/10";"0207/10";"RESISTOR, American symbol";"";"";"";"";
"R17";"2.2k";"R-US_0207/10";"0207/10";"RESISTOR, American symbol";"";"";"";"";
"R18";"2.2k";"R-US_0207/10";"0207/10";"RESISTOR, American symbol";"";"";"";"";
"R19";"1M";"R-US_0207/10";"0207/10";"RESISTOR, American symbol";"";"";"";"";
"R20";"220k";"R-US_0207/10";"0207/10";"RESISTOR, American symbol";"";"";"";"";
"R21";"220k";"R-US_0207/10";"0207/10";"RESISTOR, American symbol";"";"";"";"";
"R22";"100k";"R-US_0207/10";"0207/10";"RESISTOR, American symbol";"";"";"";"";
"R23";"220k";"R-US_0207/10";"0207/10";"RESISTOR, American symbol";"";"";"";"";
"R24";"100k";"R-US_0207/10";"0207/10";"RESISTOR, American symbol";"";"";"";"";
"R25";"100k";"R-US_0207/10";"0207/10";"RESISTOR, American symbol";"";"";"";"";
"R26";"100k";"R-US_0207/10";"0207/10";"RESISTOR, American symbol";"";"";"";"";
"R27";"130k";"R-US_0207/10";"0207/10";"RESISTOR, American symbol";"";"";"";"";
"R28";"130k";"R-US_0207/10";"0207/10";"RESISTOR, American symbol";"";"";"";"";
"R29";"130k";"R-US_0207/10";"0207/10";"RESISTOR, American symbol";"";"";"";"";
"R30";"130k";"R-US_0207/10";"0207/10";"RESISTOR, American symbol";"";"";"";"";
"R31";"130k";"R-US_0207/10";"0207/10";"RESISTOR, American symbol";"";"";"";"";
"R32";"130k";"R-US_0207/10";"0207/10";"RESISTOR, American symbol";"";"";"";"";
"R33";"100k";"R-US_0207/10";"0207/10";"RESISTOR, American symbol";"";"";"";"";
"R34";"100k";"R-US_0207/10";"0207/10";"RESISTOR, American symbol";"";"";"";"";
"R35";"1k";"R-US_0207/10";"0207/10";"RESISTOR, American symbol";"";"";"";"";
"T1";"3904";"2N3904-NPN-TO92-EBC";"TO92-EBC";"NPN Transistror";"";"";"";"";
"T2";"3904";"2N3904-NPN-TO92-EBC";"TO92-EBC";"NPN Transistror";"";"";"";"";
"T3";"3904";"2N3904-NPN-TO92-EBC";"TO92-EBC";"NPN Transistror";"";"";"";"";
"T4";"3904";"2N3904-NPN-TO92-EBC";"TO92-EBC";"NPN Transistror";"";"";"";"";
"T5";"3906";"2N3906-PNP-TO92-EBC";"TO92-EBC";"PNP Transistror";"";"";"";"";
"T6";"3906";"2N3906-PNP-TO92-EBC";"TO92-EBC";"PNP Transistror";"";"";"";"";
"T7";"3906";"2N3906-PNP-TO92-EBC";"TO92-EBC";"PNP Transistror";"";"";"";"";
"T8";"3906";"2N3906-PNP-TO92-EBC";"TO92-EBC";"PNP Transistror";"";"";"";"";
"T9";"3904";"2N3904-NPN-TO92-EBC";"TO92-EBC";"NPN Transistror";"";"";"";"";
"T10";"3904";"2N3904-NPN-TO92-EBC";"TO92-EBC";"NPN Transistror";"";"";"";"";
"T11";"3906";"2N3906-PNP-TO92-EBC";"TO92-EBC";"PNP Transistror";"";"";"";"";
"T12";"3906";"2N3906-PNP-TO92-EBC";"TO92-EBC";"PNP Transistror";"";"";"";"";

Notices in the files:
parts and their libraries:
SparkFun-Connectors: Licensing: Creative Commons ShareAlike 4.0 International - https://creativecommons.org/licenses/by-sa/4.0
